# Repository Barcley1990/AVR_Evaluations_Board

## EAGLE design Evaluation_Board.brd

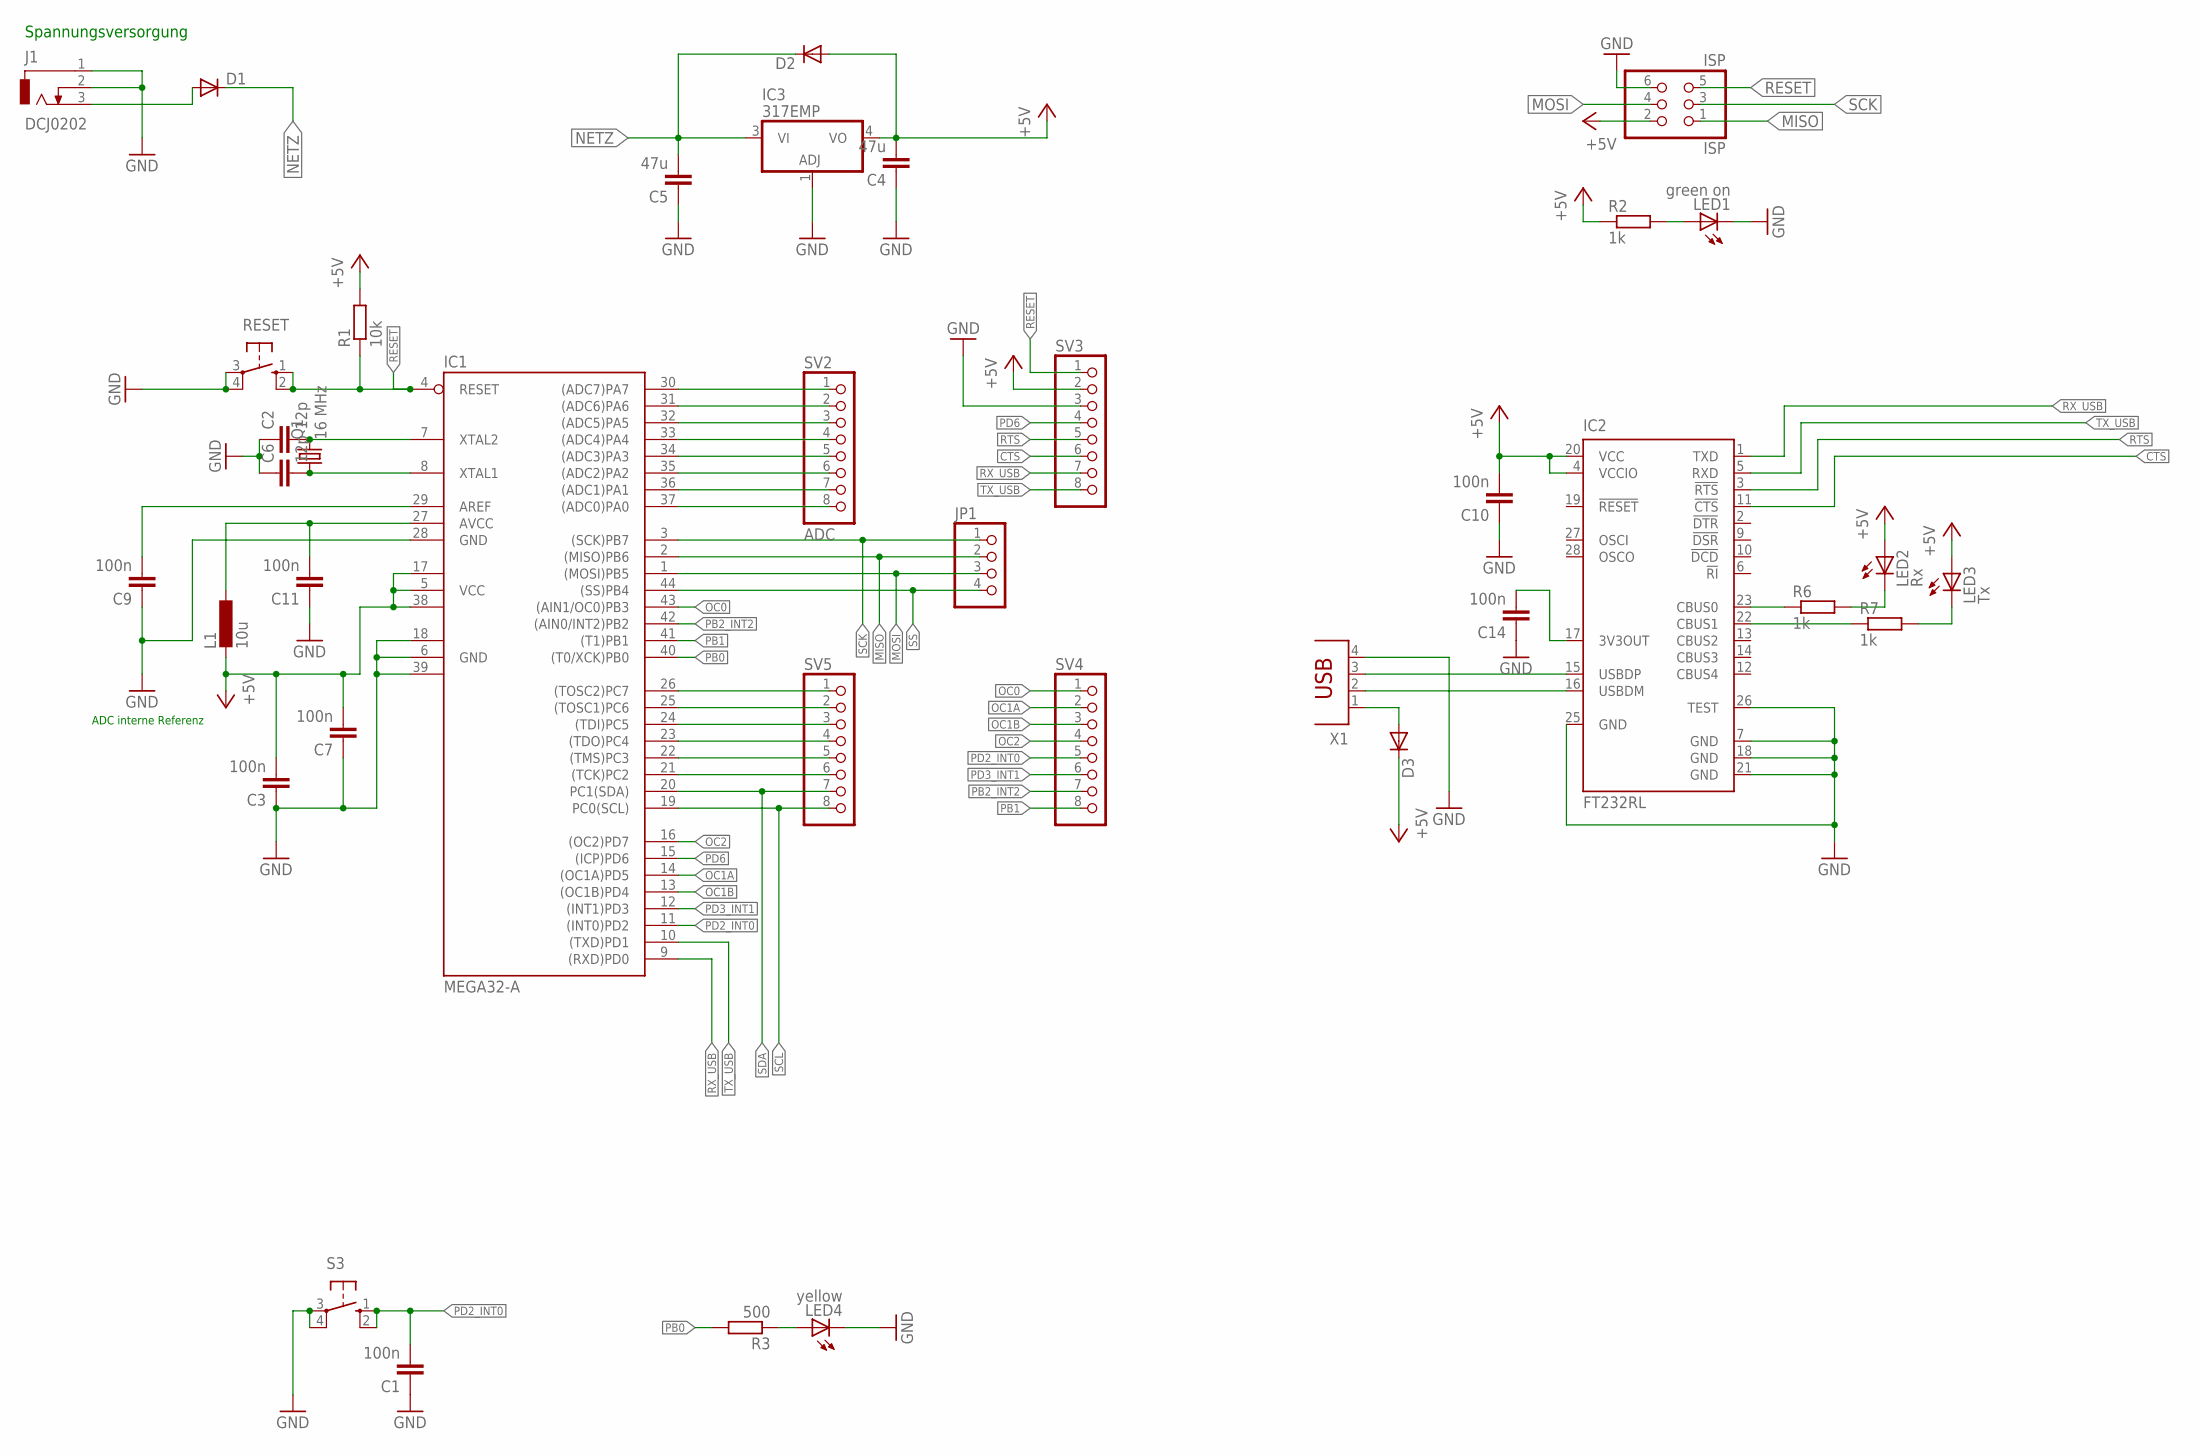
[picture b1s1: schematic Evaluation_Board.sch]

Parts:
C1, C3, C7, C9, C10, C11, C14: 100n; C0805
C2, C6: 12p; C0805
C4, C5: 47u; C0805
D1, D2, D3: DIODE-MINIMELF; MINIMELF
IC1: MEGA32-A; TQFP44
IC2: FT232RL; SSOP28
IC3: 317EMP; SOT223
ISP: ISP; 2X03
J1: DCJ0202
JP1: PINHD-1X4; 1X04
L1: 10u; L3225M
LED1: green on; SML0805
LED2: Rx; SML0805
LED3: Tx; SML0805
LED4: yellow; SML0805
Q1: 16 MHz; HC49UP
R1: 10k; R0805
R2, R6, R7: 1k; R0805
R3: 500; R0805
RESET: 10-XX; B3F-10XX
S3: 10-XX; B3F-10XX
SV2: ADC; 1X08
SV3, SV4, SV5: PINHD-1X8; 1X08
X1: USB-B-BUCHSE-HORIZONTAL

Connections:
+5V: C3.2, C4.2, C7.2, C10.2, D2.A, D3.C, IC1.5 (VCC), IC1.17 (VCC1), IC1.38 (VCC2), IC2.4 (VCCIO), IC2.20 (VCC), IC3.4 (VO), ISP.2, L1.2, LED2.A, LED3.A, R1.2, R2.1, SV3.2
CTS: IC2.11 (!CTS), SV3.6
GND: C1.1, C2.1, C3.1, C4.1, C5.1, C6.1, C7.1, C9.1, C10.1, C11.1, C14.1, IC1.6 (GND), IC1.18 (GND1), IC1.28 (GND), IC1.39 (GND2), IC2.7 (GND), IC2.18 (GND), IC2.21 (GND), IC2.25 (GND), IC2.26 (TEST), IC3.1 (ADJ), ISP.6, J1.1, J1.2, LED1.C, LED4.C, RESET.3, RESET.4 (P1), S3.3, S3.4 (P1), SV3.3, X1.4
MISO: IC1.2 ((MISO)PB6), ISP.1, JP1.2
MOSI: IC1.1 ((MOSI)PB5), ISP.4, JP1.3
unnamed: D3.A, X1.1
unnamed: D1.A, J1.3
unnamed: IC2.23 (CBUS0), R6.1
unnamed: LED1.A, R2.2
unnamed: IC1.30 ((ADC7)PA7), SV2.1
unnamed: IC1.31 ((ADC6)PA6), SV2.2
unnamed: IC1.32 ((ADC5)PA5), SV2.3
unnamed: IC1.33 ((ADC4)PA4), SV2.4
unnamed: IC1.34 ((ADC3)PA3), SV2.5
unnamed: IC1.35 ((ADC2)PA2), SV2.6
unnamed: IC1.36 ((ADC1)PA1), SV2.7
unnamed: IC1.37 ((ADC0)PA0), SV2.8
unnamed: LED2.C, R6.2
unnamed: IC2.22 (CBUS1), R7.1
unnamed: LED3.C, R7.2
unnamed: C2.2, IC1.7 (XTAL2), Q1.2
unnamed: IC2.15 (USBDP), X1.3
unnamed: IC2.16 (USBDM), X1.2
unnamed: C14.2, IC2.17 (3V3OUT)
unnamed: C6.2, IC1.8 (XTAL1), Q1.1
unnamed: LED4.A, R3.1
unnamed: C9.2, IC1.29 (AREF)
unnamed: C11.2, IC1.27 (AVCC), L1.1
unnamed: IC1.21 ((TCK)PC2), SV5.6
unnamed: IC1.22 ((TMS)PC3), SV5.5
unnamed: IC1.23 ((TDO)PC4), SV5.4
unnamed: IC1.24 ((TDI)PC5), SV5.3
unnamed: IC1.25 ((TOSC1)PC6), SV5.2
unnamed: IC1.26 ((TOSC2)PC7), SV5.1
NETZ: C5.2, D1.C, D2.C, IC3.3 (VI)
OC0: IC1.43 ((AIN1/OC0)PB3), SV4.1
OC1A: IC1.14 ((OC1A)PD5), SV4.2
OC1B: IC1.13 ((OC1B)PD4), SV4.3
OC2: IC1.16 ((OC2)PD7), SV4.4
PB0: IC1.40 ((T0/XCK)PB0), R3.2
PB1: IC1.41 ((T1)PB1), SV4.8
PB2_INT2: IC1.42 ((AIN0/INT2)PB2), SV4.7
PD2_INT0: C1.2, IC1.11 ((INT0)PD2), S3.1 (S), S3.2 (S1), SV4.5
PD3_INT1: IC1.12 ((INT1)PD3), SV4.6
PD6: IC1.15 ((ICP)PD6), SV3.4
RESET: IC1.4 (RESET), ISP.5, R1.1, RESET.1 (S), RESET.2 (S1), SV3.1
RTS: IC2.3 (!RTS), SV3.5
RX_USB: IC1.9 ((RXD)PD0), IC2.1 (TXD), SV3.7
SCK: IC1.3 ((SCK)PB7), ISP.3, JP1.1
SCL: IC1.19 (PC0(SCL)), SV5.8
SDA: IC1.20 (PC1(SDA)), SV5.7
SS: IC1.44 ((SS)PB4), JP1.4
TX_USB: IC1.10 ((TXD)PD1), IC2.5 (RXD), SV3.8

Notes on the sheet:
ADC interne Referenz
Spannungsversorgung

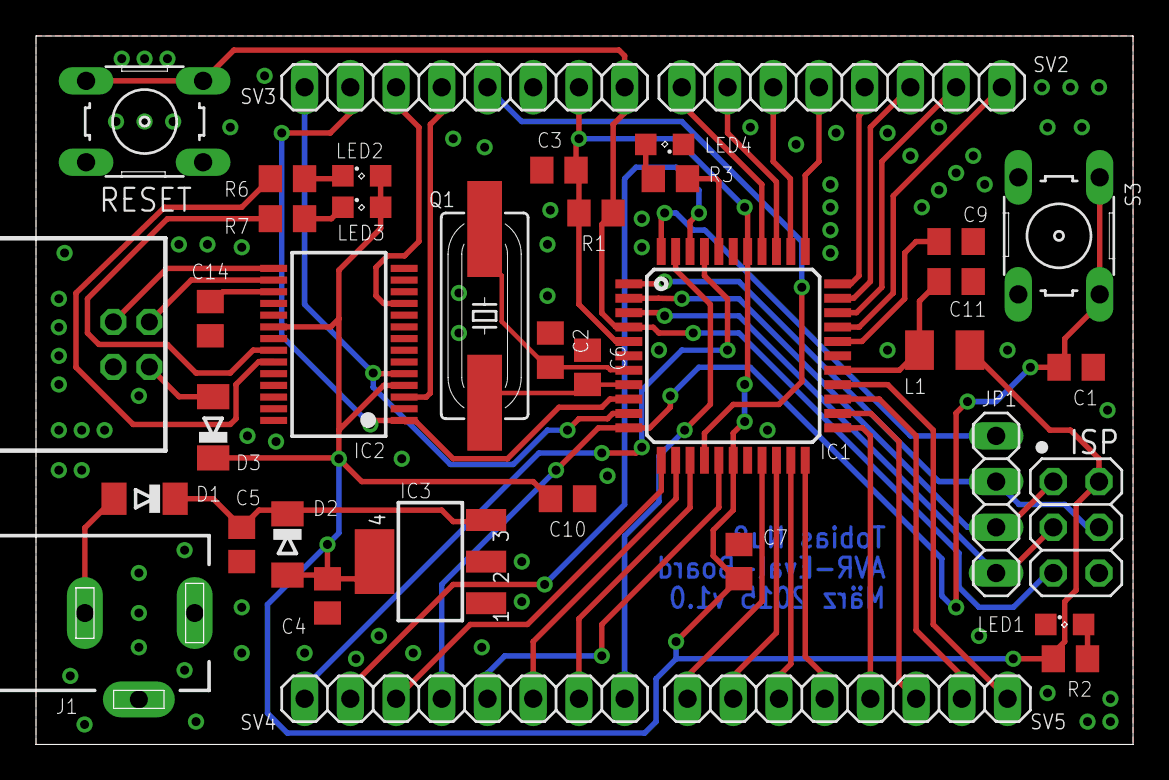
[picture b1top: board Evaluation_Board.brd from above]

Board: 2 copper layers, 60.9 x 39.4 mm, 38 parts (0 on the bottom side), 53 nets.

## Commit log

2015-03-07 Evaluations Board
2015-03-07 Changed dimension layer to 0 mil -> standard for board outline. Smashed all components to move them and get a better silk screen.
2015-03-07 Added crystal to layout and changed the values for both load caps.
2015-03-07 Begin of revolution! ;-)
2015-03-07 No airwires left, implemented crystal layout and removed the resistors on serial line. Removed diode D2 from voltage regulator and placed as anti parallel diode.
2015-03-07 Added measures. Placed all silk screen prints. PCB text now on bottom layer.
2015-03-07 Added name for ISP connector and placed a pin-one-marker on silk screen layer.
